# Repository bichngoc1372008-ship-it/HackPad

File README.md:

# HackPad
Small keyboard with 6 keys

### Inspiration

I wanted to create a macropad that allowed me to fidget. I created a macropad using 6 switches, 1 rp2040, and 4 leds. 

### Challenges

This is my second time using Fusion 360, and it took a while for me to get the hang of it! I'm still quite proud that it's my first-ever hardware project. 

### Specifications

BOM: 
- 6x Cherry MX Switches
- 4x SK6812 MINI Leds
- 1x XIAO RP2040
- 6x Blank DSA Keycaps
- 330 ohms resistor
- 4x M3x16 Bolt
- 4x M3 Heatset

Others:
- KMK Firmware
- Top Case.stl 
- Bottom Case.stl

Schematic            |  PCB         |   Case
:-------------------------:|:-------------------------:|:-------------------------:|
   |    |

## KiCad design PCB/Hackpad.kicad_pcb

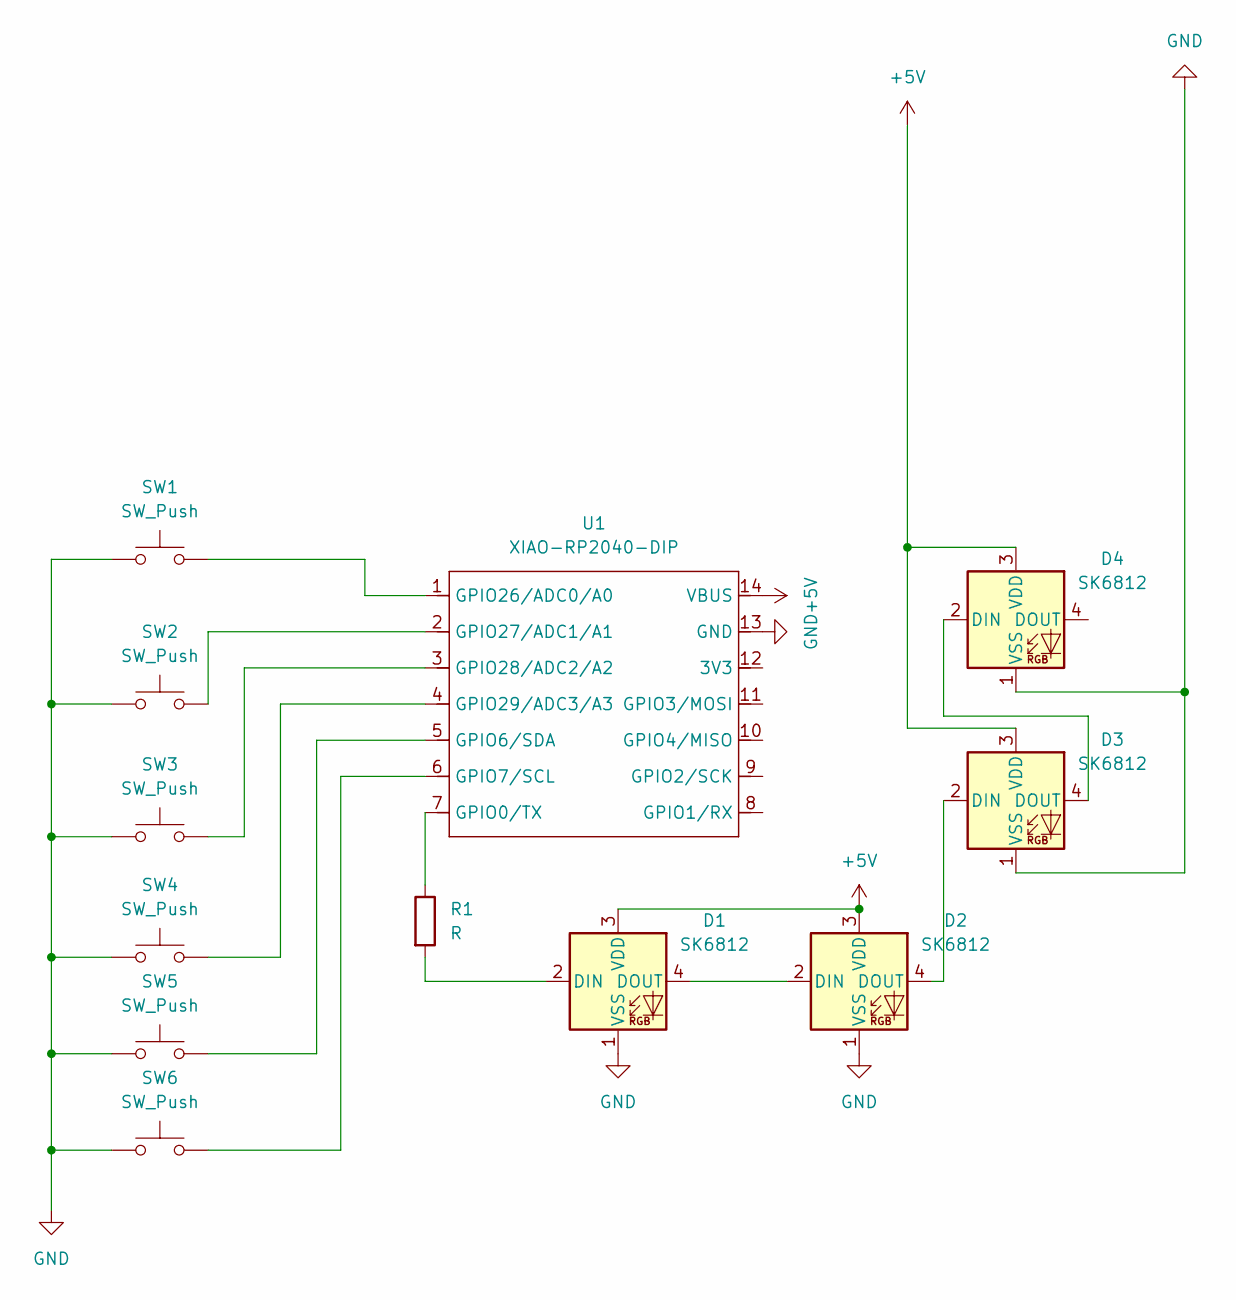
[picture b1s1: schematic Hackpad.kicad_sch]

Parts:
D1, D2, D3, D4: SK6812; LED_SK6812MINI_PLCC4_3.5x3.5mm_P1.75mm
R1: R; R_0603_1608Metric
SW1, SW2, SW3, SW4, SW5, SW6: SW_Push; SW_Cherry_MX_1.00u_PCB
U1: XIAO-RP2040-DIP

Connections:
+5V: D1.3 (VDD), D2.3 (VDD), D3.3 (VDD), D4.3 (VDD), U1.14 (VBUS)
GND: D1.1 (VSS), D2.1 (VSS), D3.1 (VSS), D4.1 (VSS), SW1.1, SW2.1, SW3.1, SW4.1, SW5.1, SW6.1, U1.13 (GND)
unnamed: D1.2 (DIN), R1.2
unnamed: D1.4 (DOUT), D2.2 (DIN)
unnamed: D2.4 (DOUT), D3.2 (DIN)
unnamed: D3.4 (DOUT), D4.2 (DIN)
unnamed: R1.1, U1.7 (GPIO0/TX)
unnamed: SW5.2, U1.5 (GPIO6/SDA)
unnamed: SW6.2, U1.6 (GPIO7/SCL)
unnamed: SW1.2, U1.1 (GPIO26/ADC0/A0)
unnamed: SW2.2, U1.2 (GPIO27/ADC1/A1)
unnamed: SW3.2, U1.3 (GPIO28/ADC2/A2)
unnamed: SW4.2, U1.4 (GPIO29/ADC3/A3)

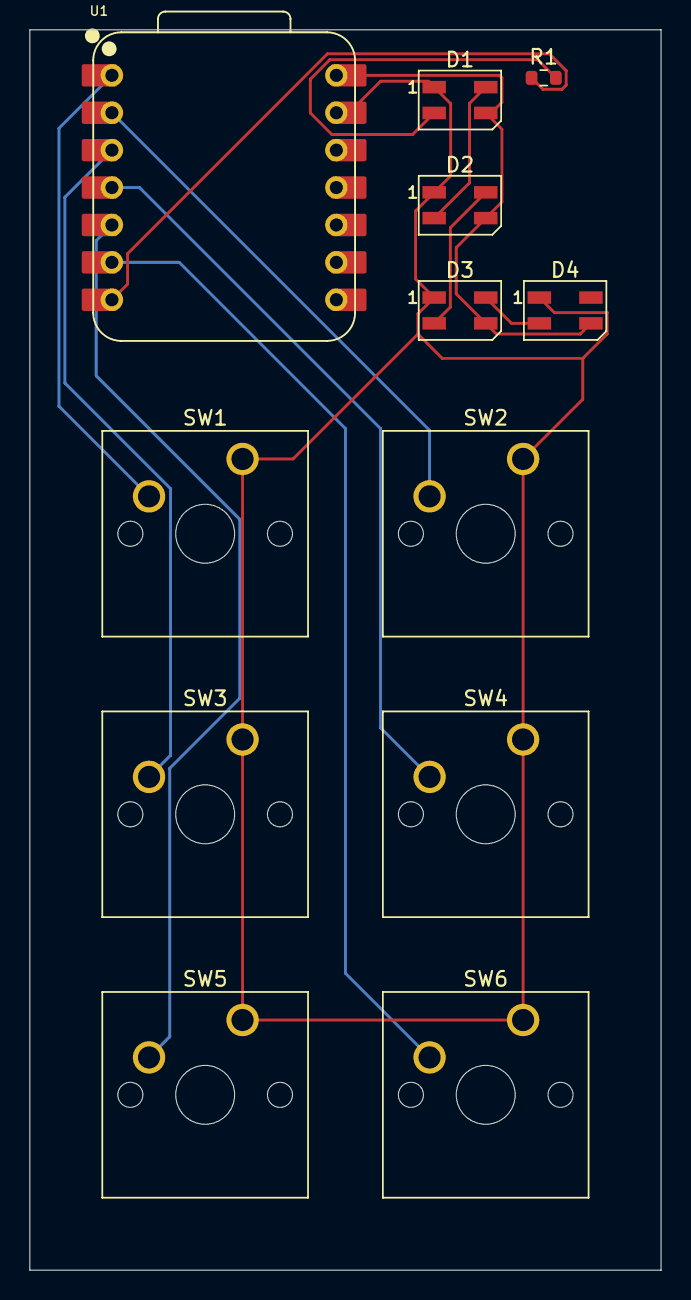
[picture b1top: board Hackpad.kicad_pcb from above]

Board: 2 copper layers, 42.9 x 84.2 mm, 12 parts (0 on the bottom side), 13 nets.

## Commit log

2026-01-17 Create CAD
